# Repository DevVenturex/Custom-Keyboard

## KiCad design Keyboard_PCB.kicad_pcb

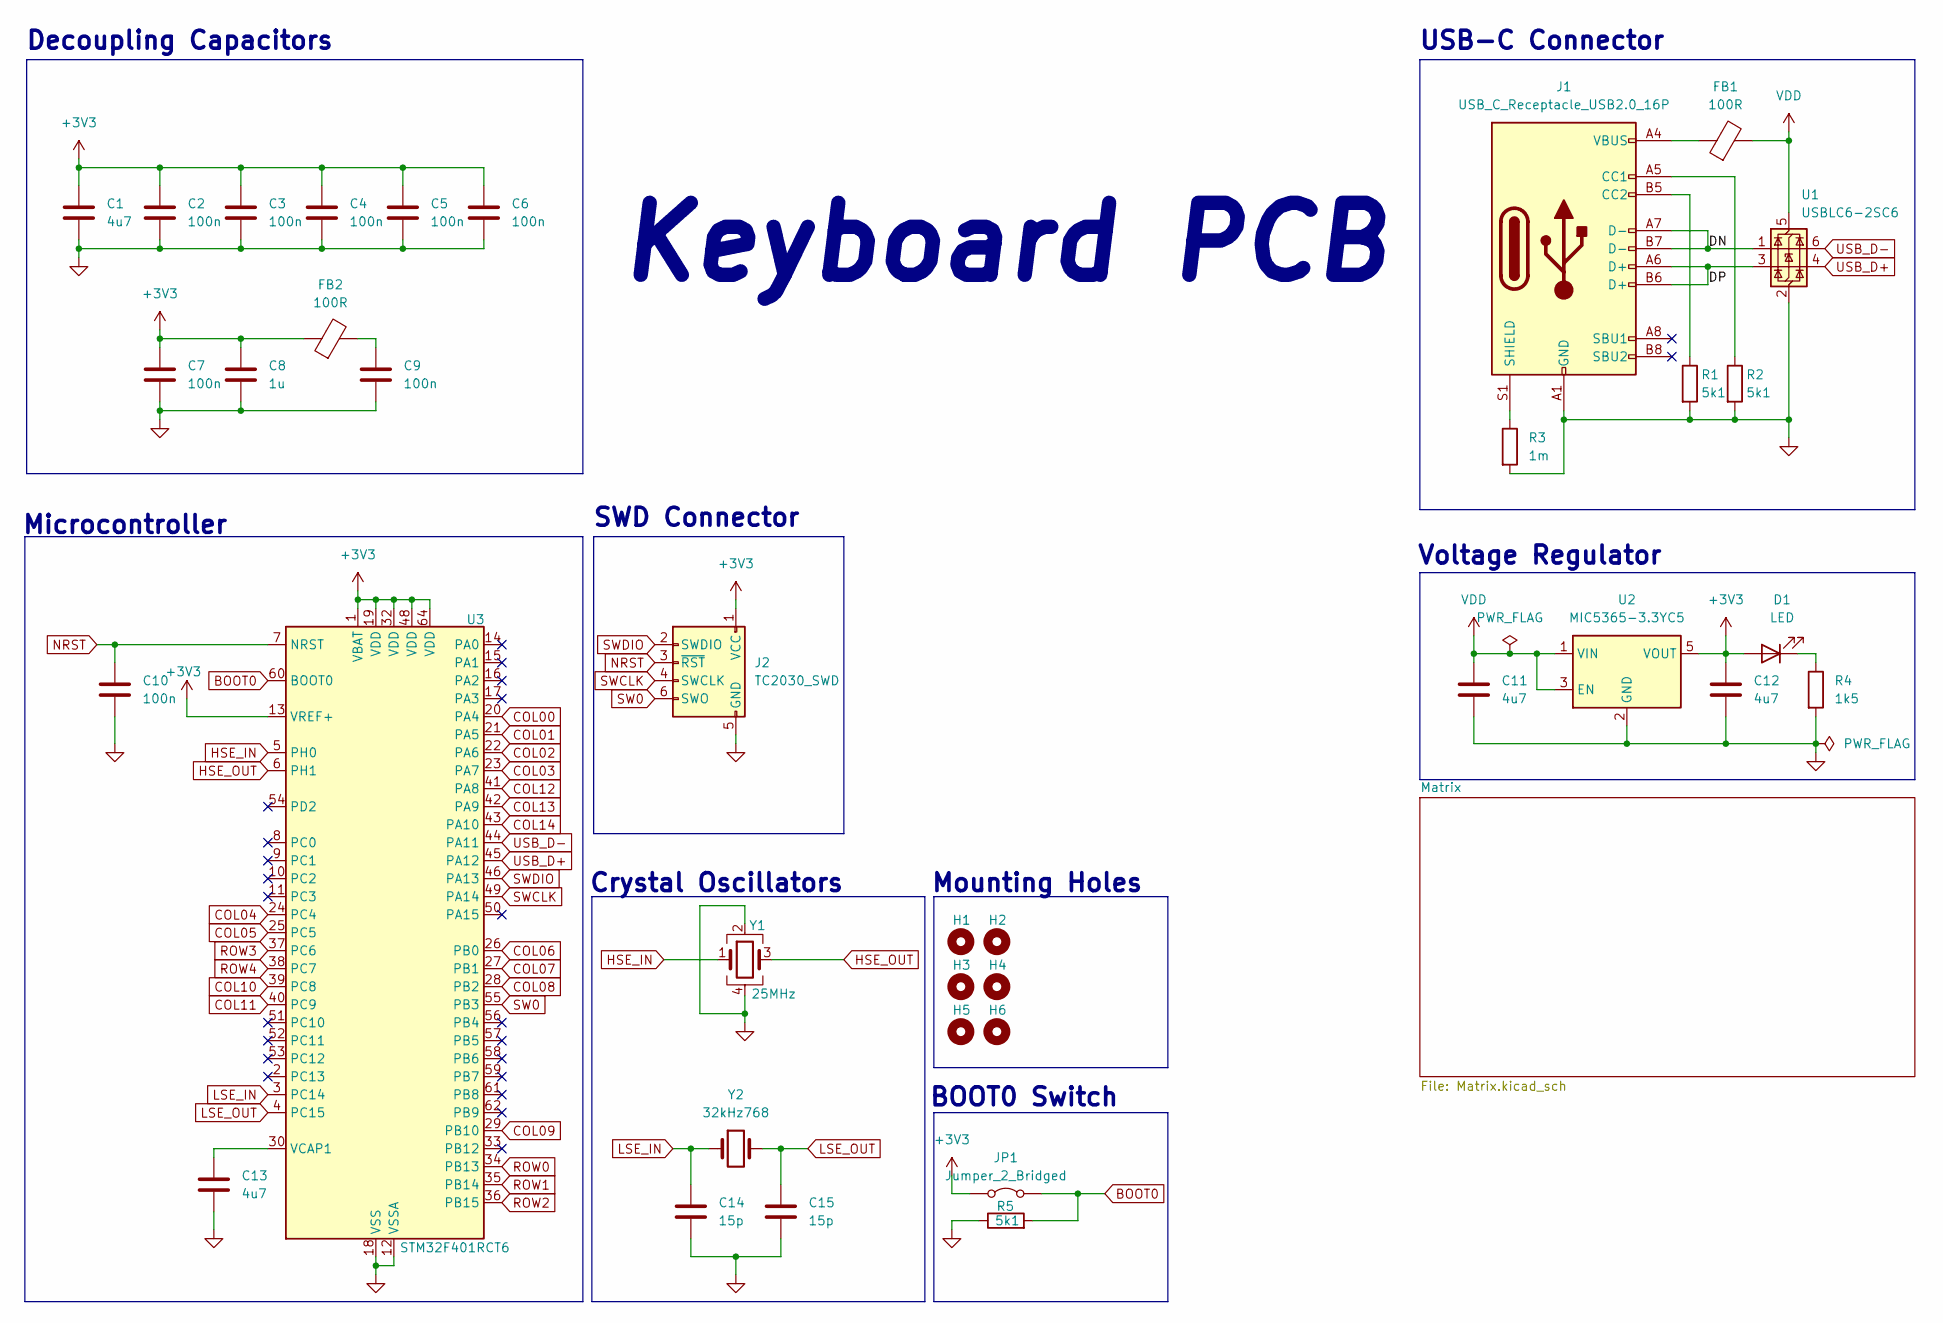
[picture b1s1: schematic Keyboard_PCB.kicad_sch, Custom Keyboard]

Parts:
C1, C11, C12, C13: 4u7; C_0805_2012Metric
C2, C3, C4, C5, C6, C7, C9, C10: 100n; C_0805_2012Metric
C8: 1u; C_0805_2012Metric
C14, C15: 15p; C_0805_2012Metric
D1: LED; LED_1206_3216Metric
FB1, FB2: 100R; L_1206_3216Metric
H1, H2, H3, H4, H5, H6: MountingHole; MountingHole_2.2mm_M2
J1: USB_C_Receptacle_USB2.0_16P; USB_C_Receptacle_HRO_TYPE-C-31-M-12
J2: TC2030_SWD; IDC-Header_2x03_P2.54mm_Horizontal
JP1: Jumper_2_Bridged; TestPoint_2Pads_Pitch2.54mm_Drill0.8mm
R1, R2, R5: 5k1; R_1206_3216Metric
R3: 1m; R_1206_3216Metric
R4: 1k5; R_1206_3216Metric
U1: USBLC6-2SC6; SOT-23-6
U2: MIC5365-3.3YC5; SOT-353_SC-70-5
U3: STM32F401RCT6; LQFP-64_10x10mm_P0.5mm
Y1: 25MHz; Crystal_SMD_3225-4Pin_3.2x2.5mm
Y2: 32kHz768; Crystal_SMD_3215-2Pin_3.2x1.5mm

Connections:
+3V3: C1.1, C2.1, C3.1, C4.1, C5.1, C6.1, C7.1, C8.1, C12.1, D1.2 (A), FB2.1, J2.1 (VCC), JP1.1 (A), U2.5 (VOUT), U3.1 (VBAT), U3.13 (VREF+), U3.19 (VDD), U3.32 (VDD), U3.48 (VDD), U3.64 (VDD)
/DN: J1.A7 (D-), J1.B7 (D-), U1.1 (I/O1)
/DP: J1.A6 (D+), J1.B6 (D+), U1.3 (I/O2)
BOOT0: JP1.2 (B), R5.2, U3.60 (BOOT0)
COL00: U3.20 (PA4); also elsewhere on the board
COL01: U3.21 (PA5); also elsewhere on the board
COL02: U3.22 (PA6); also elsewhere on the board
COL03: U3.23 (PA7); also elsewhere on the board
COL04: U3.24 (PC4); also elsewhere on the board
COL05: U3.25 (PC5); also elsewhere on the board
COL06: U3.26 (PB0); also elsewhere on the board
COL07: U3.27 (PB1); also elsewhere on the board
COL08: U3.28 (PB2); also elsewhere on the board
COL09: U3.29 (PB10); also elsewhere on the board
COL10: U3.39 (PC8); also elsewhere on the board
COL11: U3.40 (PC9); also elsewhere on the board
COL12: U3.41 (PA8); also elsewhere on the board
COL13: U3.42 (PA9); also elsewhere on the board
COL14: U3.43 (PA10); also elsewhere on the board
GND: C1.2, C2.2, C3.2, C4.2, C5.2, C6.2, C7.2, C8.2, C9.2, C10.2, C11.2, C12.2, C13.2, C14.2, C15.2, J1.A1 (GND), J1.A12 (GND), J1.B1 (GND), J1.B12 (GND), J2.5 (GND), R1.2, R2.2, R3.2, R4.2, R5.1, U1.2 (GND), U2.2 (GND), U3.12 (VSSA), U3.18 (VSS), U3.31 (VSS), U3.47 (VSS), U3.63 (VSS), Y1.2, Y1.4
HSE_IN: U3.5 (PH0), Y1.1
HSE_OUT: U3.6 (PH1), Y1.3
LSE_IN: C14.1, U3.3 (PC14), Y2.1
LSE_OUT: C15.1, U3.4 (PC15), Y2.2
NRST: C10.1, J2.3 (~RST), U3.7 (NRST)
unnamed: C9.1, FB2.2
unnamed: D1.1 (K), R4.1
unnamed: FB1.1, J1.A4 (VBUS), J1.A9 (VBUS), J1.B4 (VBUS), J1.B9 (VBUS)
unnamed: J1.A5 (CC1), R2.1
unnamed: J1.B5 (CC2), R1.1
unnamed: J1.S1 (SHIELD), R3.1
unnamed: C13.1, U3.30 (VCAP1)
ROW0: U3.34 (PB13); also elsewhere on the board
ROW1: U3.35 (PB14); also elsewhere on the board
ROW2: U3.36 (PB15); also elsewhere on the board
ROW3: U3.37 (PC6); also elsewhere on the board
ROW4: U3.38 (PC7); also elsewhere on the board
SW0: J2.6 (SWO), U3.55 (PB3)
SWCLK: J2.4 (SWCLK), U3.49 (PA14)
SWDIO: J2.2 (SWDIO), U3.46 (PA13)
USB_D+: U1.4 (I/O2), U3.45 (PA12)
USB_D-: U1.6 (I/O1), U3.44 (PA11)
VDD: C11.1, FB1.2, U1.5 (VBUS), U2.1 (VIN), U2.3 (EN)

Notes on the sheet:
Mounting Holes
Microcontroller
SWD Connector
Crystal Oscillators
USB-C Connector
Keyboard PCB
Voltage Regulator
Decoupling Capacitors
BOOT0 Switch

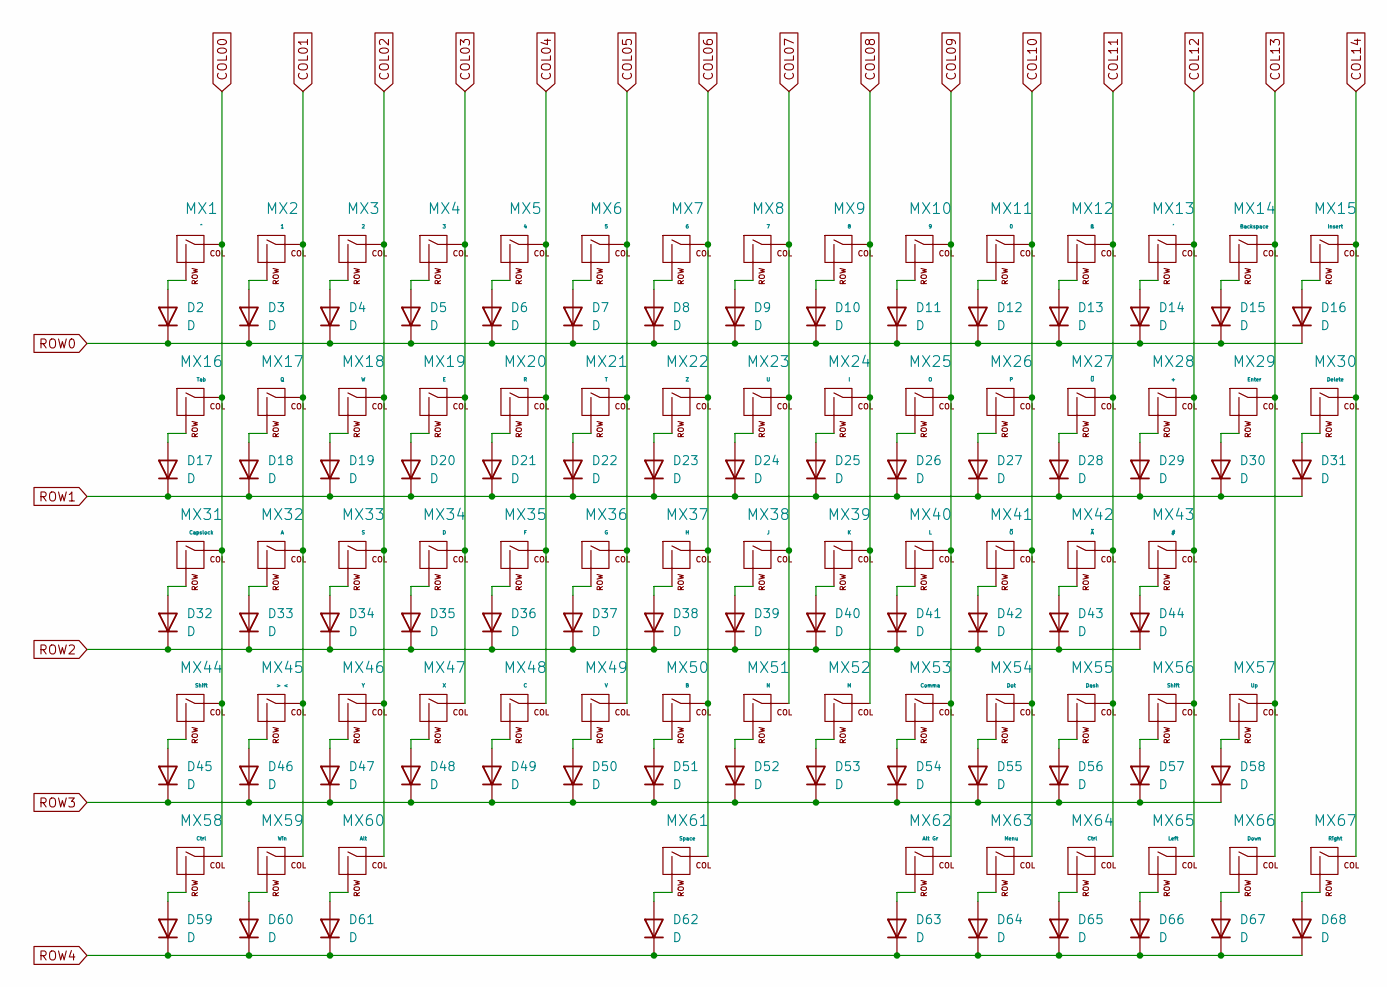
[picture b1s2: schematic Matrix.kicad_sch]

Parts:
D2, D3, D4, D5, D6, D7, D8, D9, D10, D11, D12, D13, D14, D15, D16, D17, D18, D19, D20, D21, D22, D23, D24, D25, D26, D27, D28, D29, D30, D31, D32, D33, D34, D35, D36, D37, D38, D39, D40, D41, D42, D43, D44, D45, D46, D47, D48, D49, D50, D51, D52, D53, D54, D55, D56, D57, D58, D59, D60, D61, D62, D63, D64, D65, D66, D67, D68: D; D_SOD-123
MX1: ^; MX-1U-NoLED
MX2: 1; MX-1U-NoLED
MX3: 2; MX-1U-NoLED
MX4: 3; MX-1U-NoLED
MX5: 4; MX-1U-NoLED
MX6: 5; MX-1U-NoLED
MX7: 6; MX-1U-NoLED
MX8: 7; MX-1U-NoLED
MX9: 8; MX-1U-NoLED
MX10: 9; MX-1U-NoLED
MX11: 0; MX-1U-NoLED
MX12: ß; MX-1U-NoLED
MX13: ´; MX-1U-NoLED
MX14: Backspace; MX-2U-NoLED
MX15: Insert; MX-1U-NoLED
MX16: Tab; MX-1.5U-NoLED
MX17: Q; MX-1U-NoLED
MX18: W; MX-1U-NoLED
MX19: E; MX-1U-NoLED
MX20: R; MX-1U-NoLED
MX21: T; MX-1U-NoLED
MX22: Z; MX-1U-NoLED
MX23: U; MX-1U-NoLED
MX24: I; MX-1U-NoLED
MX25: O; MX-1U-NoLED
MX26: P; MX-1U-NoLED
MX27: Ü; MX-1U-NoLED
MX28: +; MX-1U-NoLED
MX29: Enter; MXOnly-ISO-NoLED
MX30: Delete; MX-1U-NoLED
MX31: Capslock; MX-1.75U-NoLED
MX32: A; MX-1U-NoLED
MX33: S; MX-1U-NoLED
MX34: D; MX-1U-NoLED
MX35: F; MX-1U-NoLED
MX36: G; MX-1U-NoLED
MX37: H; MX-1U-NoLED
MX38: J; MX-1U-NoLED
MX39: K; MX-1U-NoLED
MX40: L; MX-1U-NoLED
MX41: Ö; MX-1U-NoLED
MX42: Ä; MX-1U-NoLED
MX43: #; MX-1U-NoLED
MX44: Shift; MX-1.25U-NoLED
MX45: > <; MX-1U-NoLED
MX46: Y; MX-1U-NoLED
MX47: X; MX-1U-NoLED
MX48: C; MX-1U-NoLED
MX49: V; MX-1U-NoLED
MX50: B; MX-1U-NoLED
MX51: N; MX-1U-NoLED
MX52: M; MX-1U-NoLED
MX53: Comma; MX-1U-NoLED
MX54: Dot; MX-1U-NoLED
MX55: Dash; MX-1U-NoLED
MX56: Shift; MX-2.25U-NoLED
MX57: Up; MX-1U-NoLED
MX58, MX64: Ctrl; MX-1.25U-NoLED
MX59: Win; MX-1U-NoLED
MX60: Alt; MX-1.25U-NoLED
MX61: Space; MX-6.25U-NoLED
MX62: Alt Gr; MX-1.25U-NoLED
MX63: Menu; MX-1.25U-NoLED
MX65: Left; MX-1U-NoLED
MX66: Down; MX-1U-NoLED
MX67: Right; MX-1U-NoLED

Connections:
COL00: MX1.1 (COL), MX16.1 (COL), MX31.1 (COL), MX44.1 (COL), MX58.1 (COL); also elsewhere on the board
COL01: MX2.1 (COL), MX17.1 (COL), MX32.1 (COL), MX45.1 (COL), MX59.1 (COL); also elsewhere on the board
COL02: MX3.1 (COL), MX18.1 (COL), MX33.1 (COL), MX46.1 (COL), MX60.1 (COL); also elsewhere on the board
COL03: MX4.1 (COL), MX19.1 (COL), MX34.1 (COL), MX47.1 (COL); also elsewhere on the board
COL04: MX5.1 (COL), MX20.1 (COL), MX35.1 (COL), MX48.1 (COL); also elsewhere on the board
COL05: MX6.1 (COL), MX21.1 (COL), MX36.1 (COL), MX49.1 (COL); also elsewhere on the board
COL06: MX7.1 (COL), MX22.1 (COL), MX37.1 (COL), MX50.1 (COL), MX61.1 (COL); also elsewhere on the board
COL07: MX8.1 (COL), MX23.1 (COL), MX38.1 (COL), MX51.1 (COL); also elsewhere on the board
COL08: MX9.1 (COL), MX24.1 (COL), MX39.1 (COL), MX52.1 (COL); also elsewhere on the board
COL09: MX10.1 (COL), MX25.1 (COL), MX40.1 (COL), MX53.1 (COL), MX62.1 (COL); also elsewhere on the board
COL10: MX11.1 (COL), MX26.1 (COL), MX41.1 (COL), MX54.1 (COL), MX63.1 (COL); also elsewhere on the board
COL11: MX12.1 (COL), MX27.1 (COL), MX42.1 (COL), MX55.1 (COL), MX64.1 (COL); also elsewhere on the board
COL12: MX13.1 (COL), MX28.1 (COL), MX43.1 (COL), MX56.1 (COL), MX65.1 (COL); also elsewhere on the board
COL13: MX14.1 (COL), MX29.1 (COL), MX57.1 (COL), MX66.1 (COL); also elsewhere on the board
COL14: MX15.1 (COL), MX30.1 (COL), MX67.1 (COL); also elsewhere on the board
unnamed: D2.2 (A), MX1.2 (ROW)
unnamed: D3.2 (A), MX2.2 (ROW)
unnamed: D4.2 (A), MX3.2 (ROW)
unnamed: D5.2 (A), MX4.2 (ROW)
unnamed: D6.2 (A), MX5.2 (ROW)
unnamed: D7.2 (A), MX6.2 (ROW)
unnamed: D8.2 (A), MX7.2 (ROW)
unnamed: D9.2 (A), MX8.2 (ROW)
unnamed: D10.2 (A), MX9.2 (ROW)
unnamed: D11.2 (A), MX10.2 (ROW)
unnamed: D12.2 (A), MX11.2 (ROW)
unnamed: D13.2 (A), MX12.2 (ROW)
unnamed: D14.2 (A), MX13.2 (ROW)
unnamed: D15.2 (A), MX14.2 (ROW)
unnamed: D16.2 (A), MX15.2 (ROW)
unnamed: D17.2 (A), MX16.2 (ROW)
unnamed: D18.2 (A), MX17.2 (ROW)
unnamed: D19.2 (A), MX18.2 (ROW)
unnamed: D20.2 (A), MX19.2 (ROW)
unnamed: D21.2 (A), MX20.2 (ROW)
unnamed: D22.2 (A), MX21.2 (ROW)
unnamed: D23.2 (A), MX22.2 (ROW)
unnamed: D24.2 (A), MX23.2 (ROW)
unnamed: D25.2 (A), MX24.2 (ROW)
unnamed: D26.2 (A), MX25.2 (ROW)
unnamed: D27.2 (A), MX26.2 (ROW)
unnamed: D28.2 (A), MX27.2 (ROW)
unnamed: D29.2 (A), MX28.2 (ROW)
unnamed: D30.2 (A), MX29.2 (ROW)
unnamed: D31.2 (A), MX30.2 (ROW)
unnamed: D32.2 (A), MX31.2 (ROW)
unnamed: D33.2 (A), MX32.2 (ROW)
unnamed: D34.2 (A), MX33.2 (ROW)
unnamed: D35.2 (A), MX34.2 (ROW)
unnamed: D36.2 (A), MX35.2 (ROW)
unnamed: D37.2 (A), MX36.2 (ROW)
unnamed: D38.2 (A), MX37.2 (ROW)
unnamed: D39.2 (A), MX38.2 (ROW)
unnamed: D40.2 (A), MX39.2 (ROW)
unnamed: D41.2 (A), MX40.2 (ROW)
unnamed: D42.2 (A), MX41.2 (ROW)
unnamed: D43.2 (A), MX42.2 (ROW)
unnamed: D44.2 (A), MX43.2 (ROW)
unnamed: D45.2 (A), MX44.2 (ROW)
unnamed: D46.2 (A), MX45.2 (ROW)
unnamed: D47.2 (A), MX46.2 (ROW)
unnamed: D48.2 (A), MX47.2 (ROW)
unnamed: D49.2 (A), MX48.2 (ROW)
unnamed: D50.2 (A), MX49.2 (ROW)
unnamed: D51.2 (A), MX50.2 (ROW)
unnamed: D52.2 (A), MX51.2 (ROW)
unnamed: D53.2 (A), MX52.2 (ROW)
unnamed: D54.2 (A), MX53.2 (ROW)
unnamed: D55.2 (A), MX54.2 (ROW)
unnamed: D56.2 (A), MX55.2 (ROW)
unnamed: D57.2 (A), MX56.2 (ROW)
unnamed: D58.2 (A), MX57.2 (ROW)
unnamed: D59.2 (A), MX58.2 (ROW)
unnamed: D60.2 (A), MX59.2 (ROW)
unnamed: D61.2 (A), MX60.2 (ROW)
unnamed: D62.2 (A), MX61.2 (ROW)
unnamed: D63.2 (A), MX62.2 (ROW)
unnamed: D64.2 (A), MX63.2 (ROW)
unnamed: D65.2 (A), MX64.2 (ROW)
unnamed: D66.2 (A), MX65.2 (ROW)
unnamed: D67.2 (A), MX66.2 (ROW)
unnamed: D68.2 (A), MX67.2 (ROW)
ROW0: D2.1 (K), D3.1 (K), D4.1 (K), D5.1 (K), D6.1 (K), D7.1 (K), D8.1 (K), D9.1 (K), D10.1 (K), D11.1 (K), D12.1 (K), D13.1 (K), D14.1 (K), D15.1 (K), D16.1 (K); also elsewhere on the board
ROW1: D17.1 (K), D18.1 (K), D19.1 (K), D20.1 (K), D21.1 (K), D22.1 (K), D23.1 (K), D24.1 (K), D25.1 (K), D26.1 (K), D27.1 (K), D28.1 (K), D29.1 (K), D30.1 (K), D31.1 (K); also elsewhere on the board
ROW2: D32.1 (K), D33.1 (K), D34.1 (K), D35.1 (K), D36.1 (K), D37.1 (K), D38.1 (K), D39.1 (K), D40.1 (K), D41.1 (K), D42.1 (K), D43.1 (K), D44.1 (K); also elsewhere on the board
ROW3: D45.1 (K), D46.1 (K), D47.1 (K), D48.1 (K), D49.1 (K), D50.1 (K), D51.1 (K), D52.1 (K), D53.1 (K), D54.1 (K), D55.1 (K), D56.1 (K), D57.1 (K), D58.1 (K); also elsewhere on the board
ROW4: D59.1 (K), D60.1 (K), D61.1 (K), D62.1 (K), D63.1 (K), D64.1 (K), D65.1 (K), D66.1 (K), D67.1 (K), D68.1 (K); also elsewhere on the board

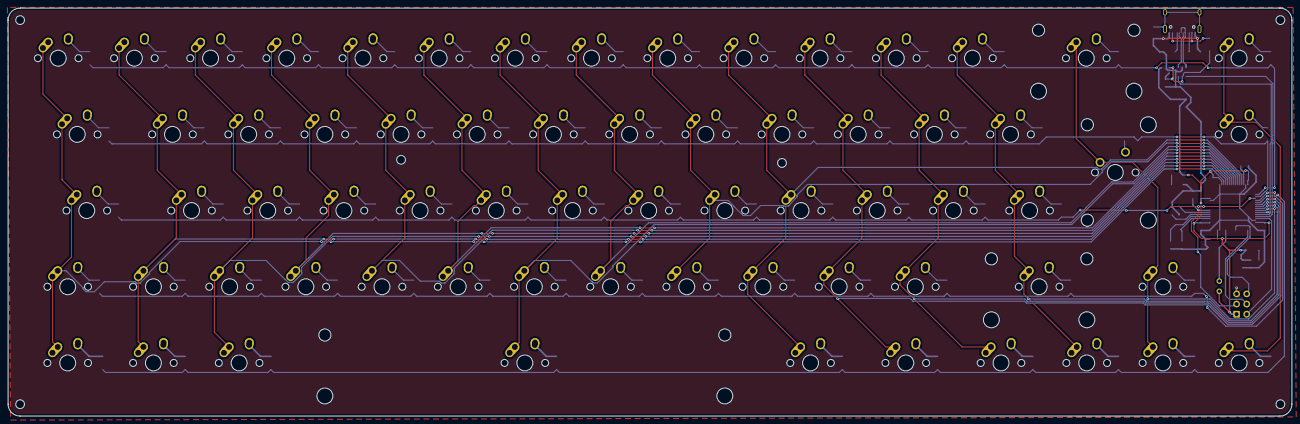
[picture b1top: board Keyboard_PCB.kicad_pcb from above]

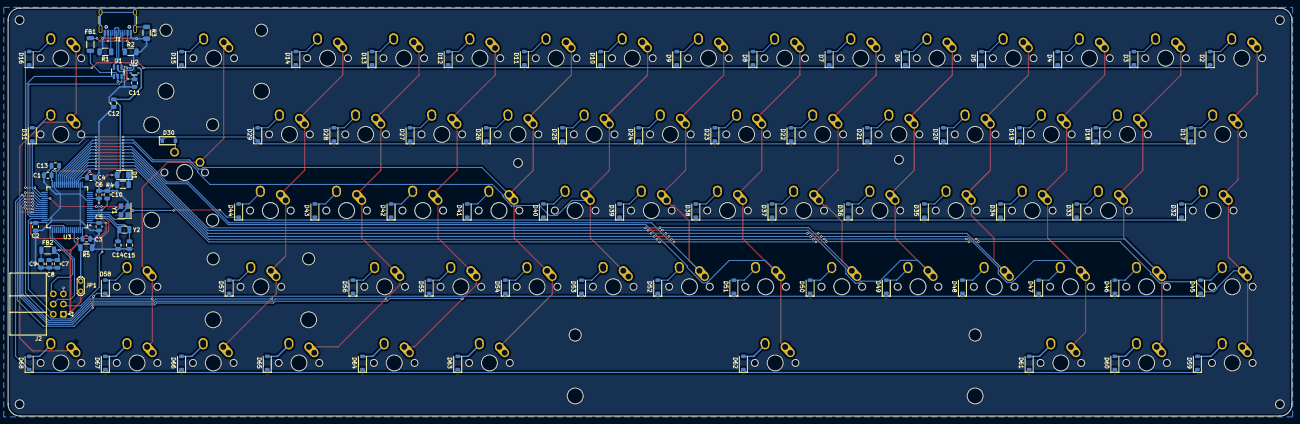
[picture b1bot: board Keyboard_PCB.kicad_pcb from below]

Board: 2 copper layers, 321.0 x 102.0 mm, 171 parts (98 on the bottom side), 110 nets.

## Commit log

2024-06-22 KiCad
2024-06-22 Most of the Routing Done
2024-06-22 Missing Matrix Connection to MCU
2024-06-23 PCB finished
2024-06-24 save
